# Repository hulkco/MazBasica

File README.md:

# MazBasica v1.0
Arduino UNO trainer shield.
Source code as included in Ardublock, which is a visual programming language, which will enable students ages 8 and up, marvelous introduction to the world of programming and physical computing.
/////
Tarjeta entrenadora para Arduino UNO.
Se incluye código fuente en Ardublock, el cual es un lenguaje de programacion visual, el cual permitira a los alumnos de 8 años en adelante, introducirse al maravillos mundo de la programacion y la computacion fisica.

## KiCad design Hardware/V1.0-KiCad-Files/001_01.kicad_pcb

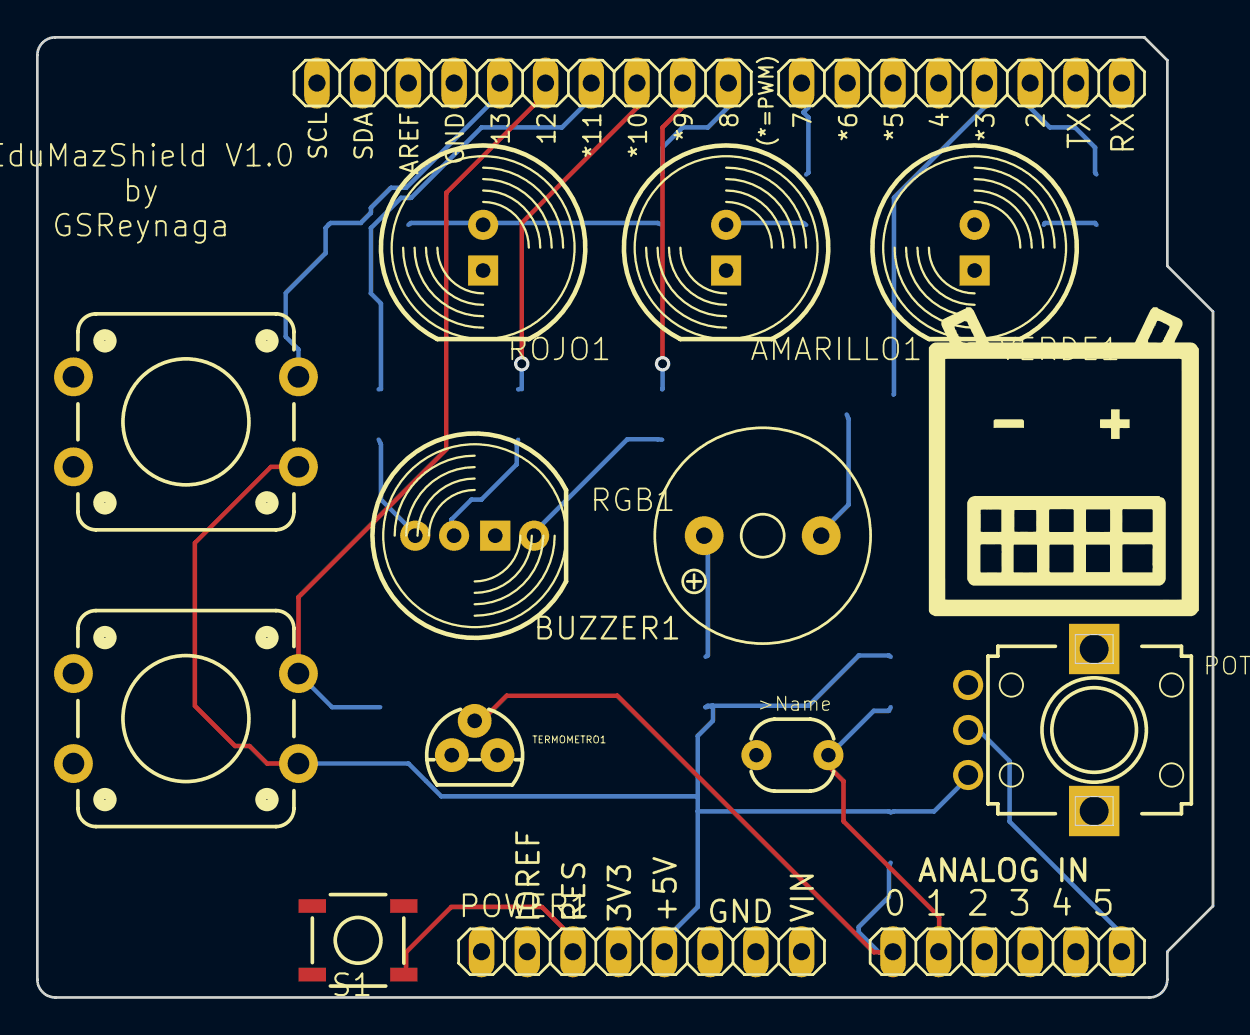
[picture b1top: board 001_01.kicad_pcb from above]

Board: 2 copper layers, 65.3 x 53.3 mm, 28 parts (0 on the bottom side), 23 nets.

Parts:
AMARILLO1: LED10MM
BOTON_A1: SWITCH-MOMENTARY-212MM; TACTILE-PTH-12MM
BOTON_B1: SWITCH-MOMENTARY-212MM; TACTILE-PTH-12MM
BUZZER1: BUZZER; F_QMBIII
JANALOG1: 6x1F-H8.5-L14.5mm; 1X06-TH
JHIGH1: 10x1F-H8.5-L14.5mm; 1X10-TH
JLOW1: 8x1F-H8.5-L14.5mm; 1X08-TH
LDR1: FOTOCELDA; PHOTOCELL
POTENCIOMETRO1: POTENCIOMETRO; EVUF
POWER1: 8x1F-H8.5-L14.5mm; 1X08-TH
Q1: FDV301N; SOT23-W
R1, R2, R3, R4, R8, R9, R12, R13, R19: 330; M1206
R7, R10: 10k; M1206
RGB1: RGB; LED-RGB-10MM
ROJO1: LED10MM
S1: TAC_SWITCHSMD; TACTILE_SWITCH_SMD
TERMOMETRO1: TERMOMETRO; LM335Z
U$1: LOGO-BOY-001
VERDE1: LED10MM

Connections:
/5V: BOTON_A1.1, BOTON_B1.1, POTENCIOMETRO1.3, POWER1.5, R4.2, R7.2, R10.2
/A0: JANALOG1.1, R7.1, TERMOMETRO1.2
/A1: JANALOG1.2, LDR1.2, R10.1
/A5: JANALOG1.6, POTENCIOMETRO1.2
/D2: JLOW1.3, R1.2
/D3: JLOW1.4, Q1.1
/D7: JLOW1.8, R2.2
/D8: JHIGH1.1, R3.2
/D9: JHIGH1.2, R9.1
/D10: JHIGH1.3, R12.1
/D11: JHIGH1.4, R13.1
/D12: BOTON_A1.3, JHIGH1.5, R8.1
/D13: BOTON_B1.3, JHIGH1.6, R19.1
/RESET: POWER1.3, S1.1
GND: AMARILLO1.K, JHIGH1.7, LDR1.1, POTENCIOMETRO1.1, POWER1.6, POWER1.7, Q1.2, R8.2, R19.2, RGB1.A, ROJO1.K, S1.3, TERMOMETRO1.1, VERDE1.K
unnamed: AMARILLO1.A, R2.1
unnamed: BUZZER1.+, R4.1
unnamed: BUZZER1.-, Q1.3
unnamed: R1.1, VERDE1.A
unnamed: R3.1, ROJO1.A
unnamed: R9.2, RGB1.CR
unnamed: R12.2, RGB1.CG
unnamed: R13.2, RGB1.CB

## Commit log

2015-12-23 Comentario
2015-12-23 Fotos
2015-12-26 Create gh-pages branch via GitHub
2016-02-25 Cambio estructura
2016-05-18 Create todo
2017-06-12 Changes 16-06-2017
    Minor changes to manual.
2017-06-12 Changes file name
    Update the file name
2017-06-12 Change Directory Name
2019-02-21 Update KiCad Files
